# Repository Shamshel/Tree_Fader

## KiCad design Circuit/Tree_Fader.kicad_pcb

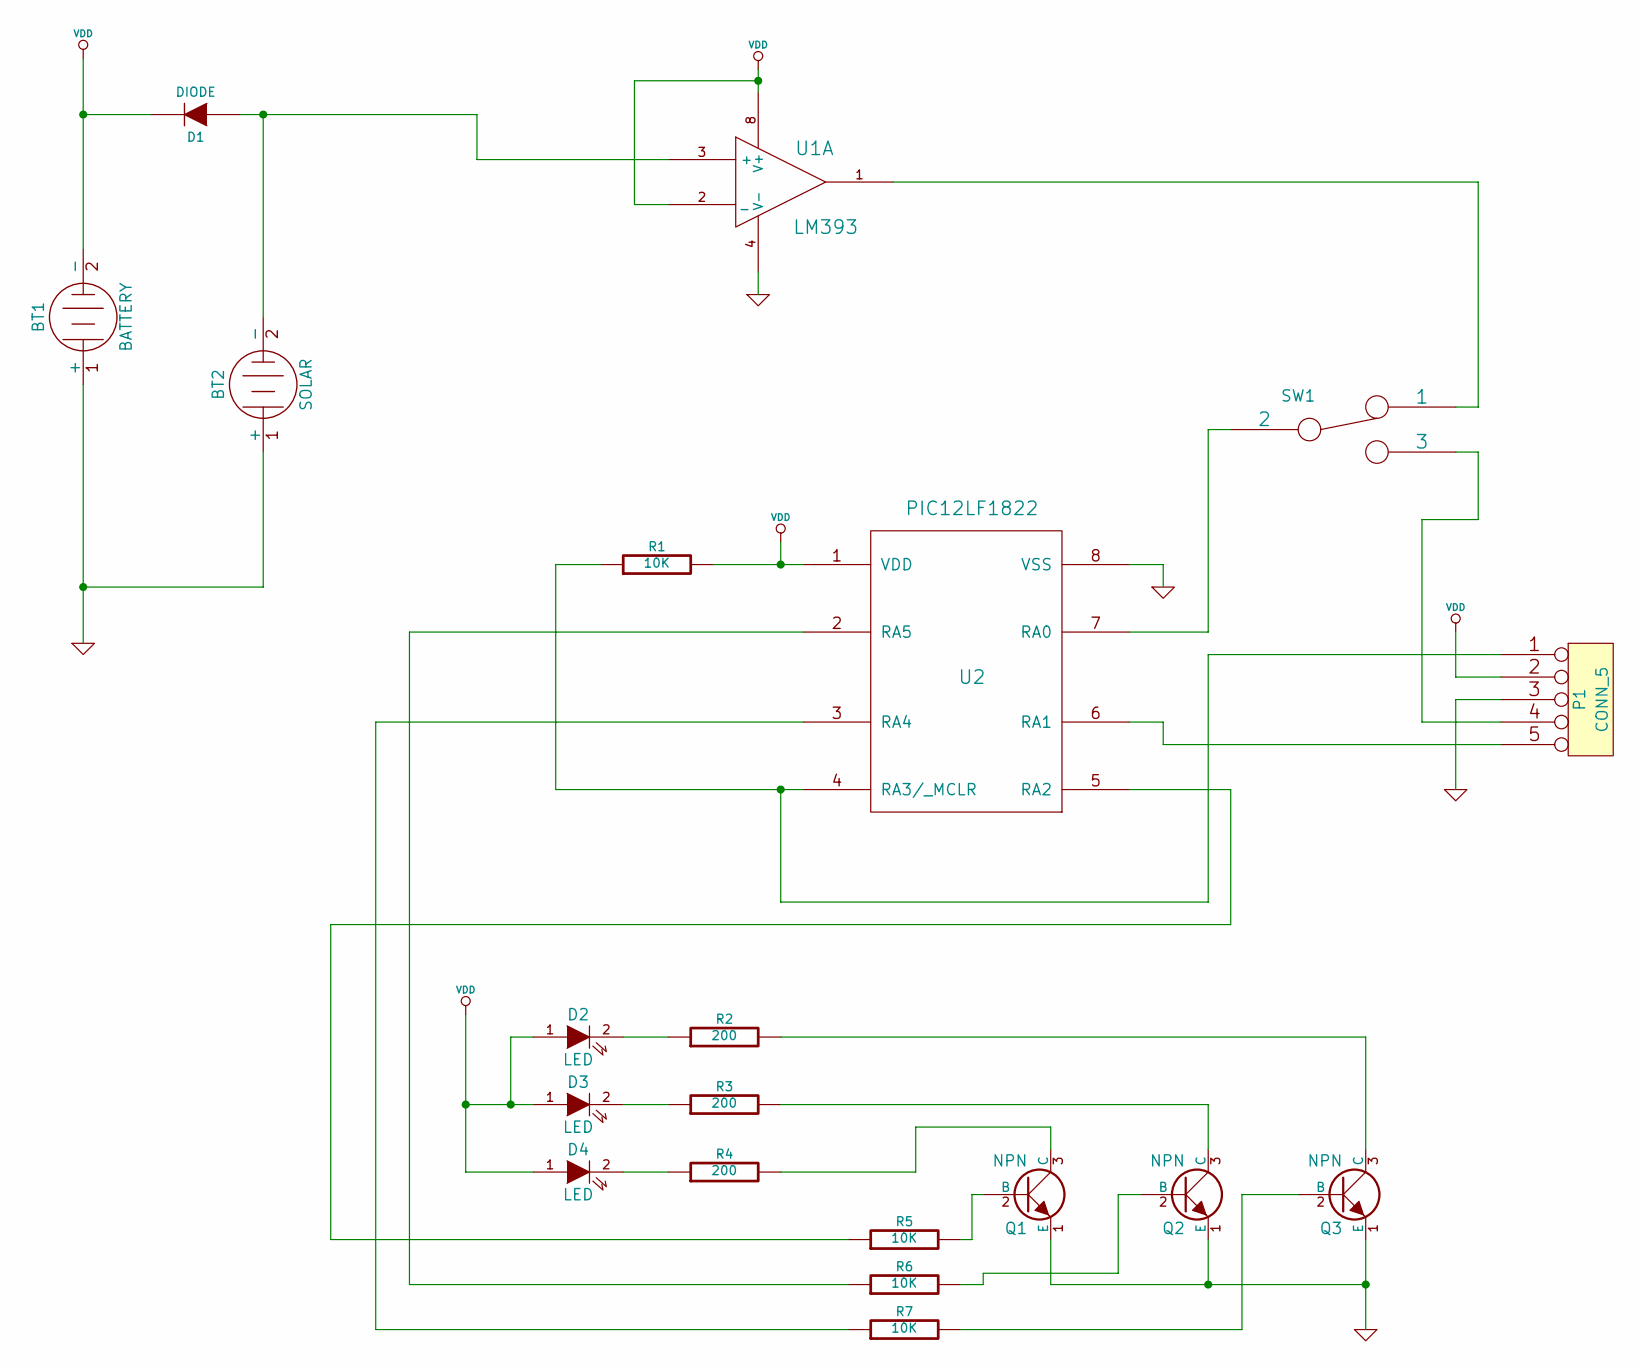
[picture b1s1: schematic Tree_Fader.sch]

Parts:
BT1: BATTERY
BT2: SOLAR
D1: DIODE
D2, D3, D4: LED
P1: CONN_5
Q1, Q2, Q3: NPN
R1, R5, R6, R7: 10K
R2, R3, R4: 200
SW1: (no value)
U1: LM393
U2: PIC12LF1822

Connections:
GND: BT1.1 (+), BT2.1 (+), P1.3, Q1.1 (E), Q2.1 (E), Q3.1 (E), U1.4 (V-), U2.8 (VSS)
unnamed: Q1.3 (C), R4.2
unnamed: Q2.3 (C), R3.2
unnamed: Q1.2 (B), R5.2
unnamed: Q3.2 (B), R7.2
unnamed: R5.1, U2.5 (RA2)
unnamed: Q3.3 (C), R2.2
unnamed: Q2.2 (B), R6.2
unnamed: P1.4, SW1.3
unnamed: SW1.1, U1.1
unnamed: R6.1, U2.2 (RA5)
unnamed: R7.1, U2.3 (RA4)
unnamed: SW1.2, U2.7 (RA0)
unnamed: D2.2 (K), R2.1
unnamed: D3.2 (K), R3.1
unnamed: BT2.2 (-), D1.1 (A), U1.3 (+)
unnamed: P1.5, U2.6 (RA1)
unnamed: P1.1, R1.1, U2.4 (RA3/_MCLR)
unnamed: D4.2 (K), R4.1
VDD: BT1.2 (-), D1.2 (K), D2.1 (A), D3.1 (A), D4.1 (A), P1.2, R1.2, U1.2 (_), U1.8 (V+), U2.1 (VDD)

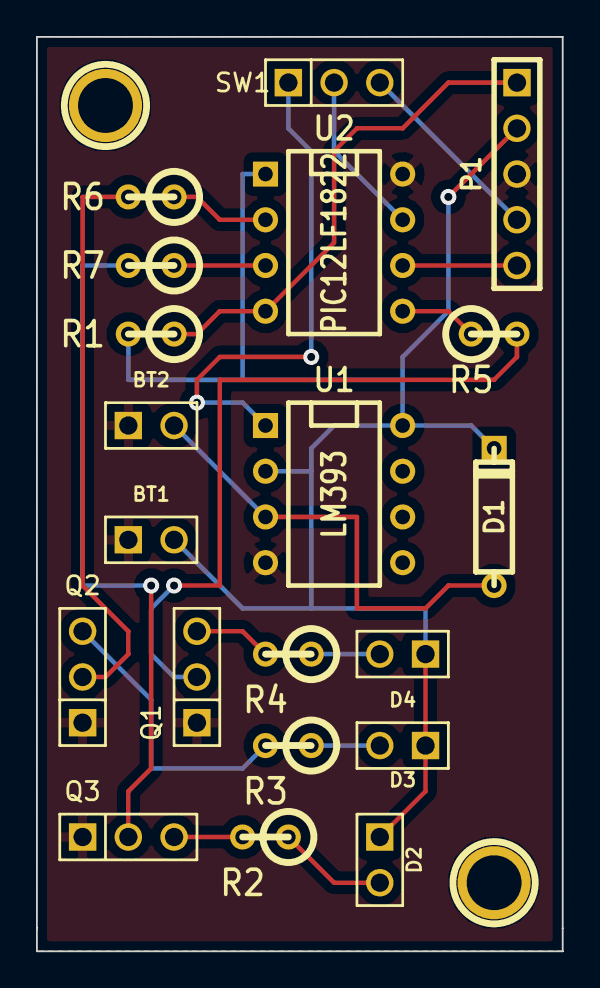
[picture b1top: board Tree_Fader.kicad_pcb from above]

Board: 2 copper layers, 29.2 x 50.8 mm, 20 parts (0 on the bottom side), 20 nets.

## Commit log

2015-05-09 :circus_tent: Added .gitattributes & .gitignore files
2015-05-11 Wrote software PWM module, added documentation
    The WDT seems to have strange effects on the program running, seems to
    reset the program after a few seconds. This could be solved with
    additional reading, but is probably unnecessary. Need to add
    additional variables to add the remaining 2 PWM outputs.
2015-05-11 Added additional PWM channels
    Added additional soft PWM channels of differing beginning duty cycle and
    direction. Need to add support for fading from start to these initial
    positions.
2015-05-15 Added Clock Switchover
    The main controller now detects the change in power source and
    automatically switches from a 1MHz clock to a 500kHz clock. The future
    revisions could use nanowatt low power mode, a specific feature of the
    LF series.
2015-05-15 Created PCB in KiCad
    Submitted order to OSH Park. Of course, resistors R4 and R3 are not
    connected to the ground of D4 and D3. This is fixed here, but the order
    was submitted, and will require a "bodge wire".
